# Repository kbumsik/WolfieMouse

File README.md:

# WolfieMouse

WolfieMouse is a robotics project to build [a micromouse](https://en.wikipedia.org/wiki/Micromouse). This project covers three parts:

* Robotics algorithm for maze solving (C++)
* low-level hardware driver software (C and ARM assembly)
* Tools to capture and plot robot's sensor data (Python)
* Embedded hardware design and PCB design (KiCad, an open-source alternative to Altium)

This robot won:
  * **The Special Mention Award in 2018 IEEE Region 1 Micromouse Robotics Competition**.
  * **The 3rd Place Award in 2019 IEEE Region 1 Micromouse Robotics Competition**.

## Get started

If you don't know what is micromouse competition, [this document will help.](doc/What-is-Micromouse.md).

Requires tools:
* [GNU Arm Embedded Toolchain](https://developer.arm.com/open-source/gnu-toolchain/gnu-rm) and [Makefile](https://www.gnu.org/software/make/manual/make.html) to build program for the robot.
* [OpenOCD](http://openocd.org/) to upload the program to the robot and to debug.
* [KiCad](http://kicad.org/) to design a PCB hardware.

Otherwise, a [Vagrant](https://www.vagrantup.com/) virtual machine environment is provided to skip installing the above tools.

If you whish to start with this project, see [get stared document](doc/Get-started.md).

## Documentation

See [documentation section.](doc/)

## Directory descriptions

* `doc`: Documentation folder
* `firmware`: The robot's program folder, including robotics algorithms and hardware drivers
* `simulation`: Programs to test algorithms on a desktop computer
* `tools`: Contains robot sensor data capturing tools and scripts for Vagrant machine.

## Gallery

Terminal-based simulation program. `M` stands for the position of the robot, `D` stands for the position of the goal in the maze, and `S` stands for the starting position.

Schematic overview.

PCB Footprint overview.

## License and Credits

Source code in `firmware` and `simulation` folders are licensed under [GPLv2.1](https://www.gnu.org/licenses/old-licenses/lgpl-2.1.en.html).

External libraries (FreeRTOS, CMSIS, STM32F4 HAL) under `firmware/lib` follow their own terms.

The fundamental hardware design is inspired by [Project Futura](http://micromouseusa.com/?page_id=1342) by [Green Ye](http://www.greenye.net/).

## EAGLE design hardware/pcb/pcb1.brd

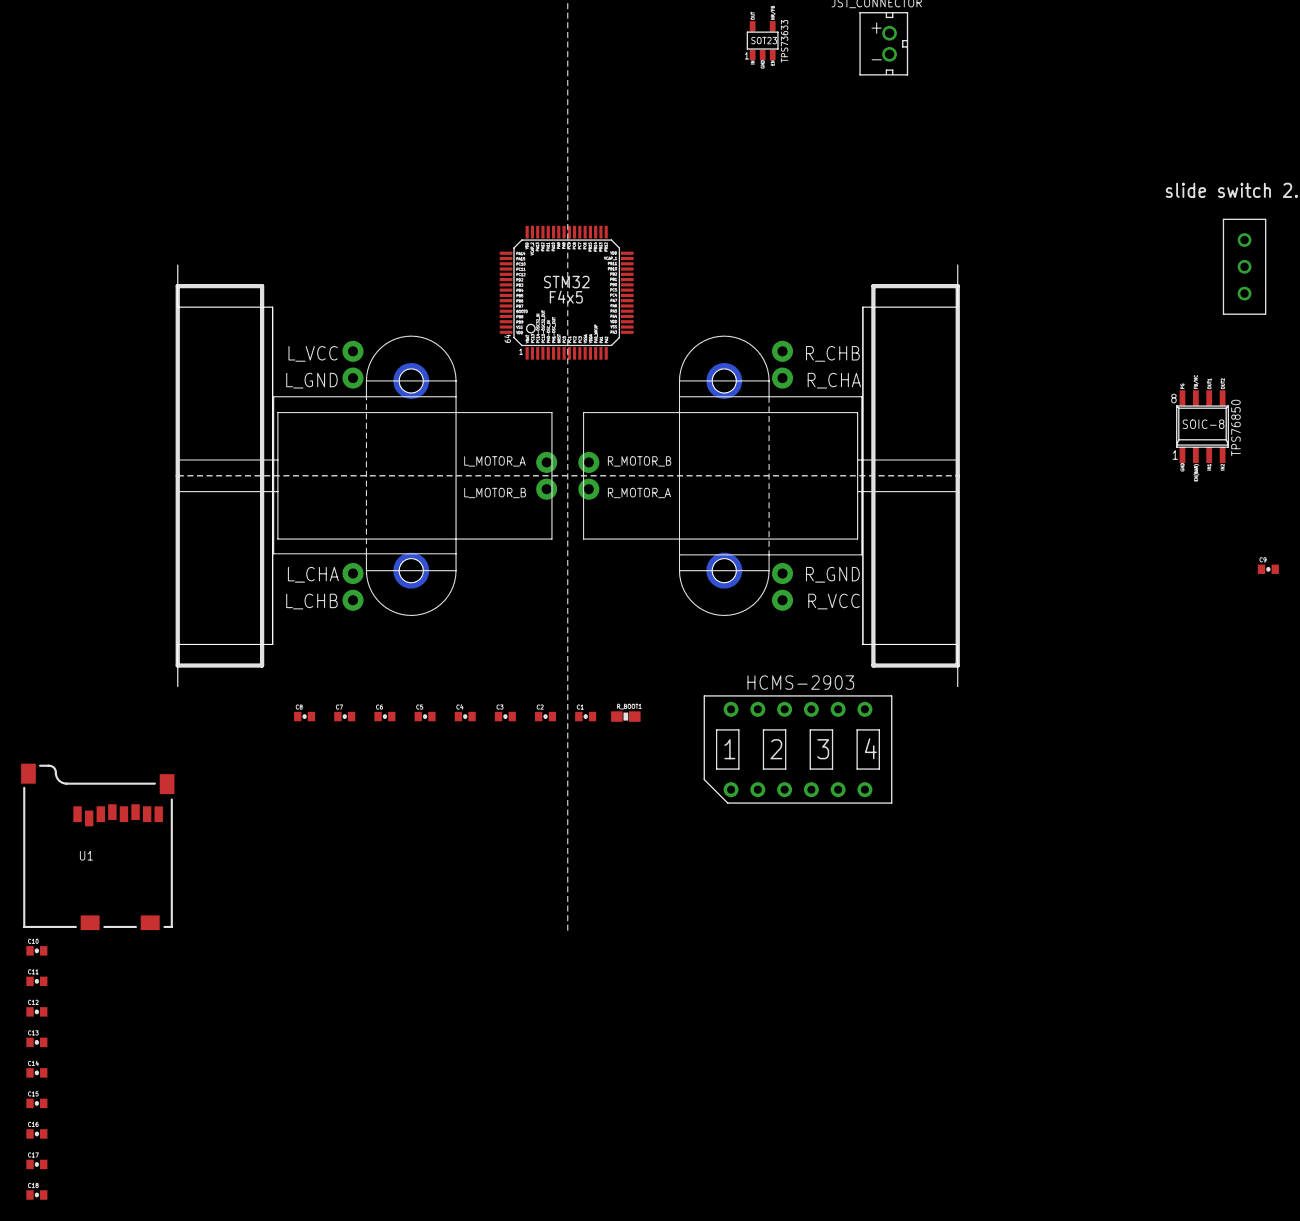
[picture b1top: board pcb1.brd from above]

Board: 2 copper layers, 27 parts (0 on the bottom side), 14 nets, no tracks yet.

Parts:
C1, C8: 2.2uF; 0402-CAP
C2, C3, C6, C7, C9, C10, C11, C12, C13, C14, C15, C16, C17, C18: 0.1uF; 0402-CAP
C4, C5: 4.7uF; 0402-CAP
R_BOOT1: 47K; 0603-RES
U1: USD-SOCKETSMD; MICRO-SD-SOCKET-PP
U$1: FUTURA_V1.0_MOTOR_MOUNT; FUTURA_V1.0_MOTOT_MOUNT
U$2: STM32F405/415_LQFP64
U$3: TPS76850(SOIC-8)
U$4: TPS73633(SOT-23)
U$5: JST_CONNECTOR_FEMALE
U$6: TS02_SWITCH
U$7: HCMS-2903

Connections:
3.3V: C2.1, C3.1, C4.1, C5.1, C6.1, C7.2, C9.1, C14.2, C15.2, C16.2, U$2.VBAT, U$2.VDDA, U$2.VDD_0, U$2.VDD_1, U$2.VDD_2, U$2.VDD_3, U$4.NR/FB, U$4.OUT
5V: C17.2, C18.2, U$7.SEL, U$7.V_LOGIC
AGND: C5.2, C6.2, U$2.VSSA
DIS_CE: U$2.PC11, U$7.CE
DIS_DATA_IN: U$2.PB5, U$7.DATA_IN
DIS_RESET: U$2.PC10, U$7.RESET
DIS_RS: U$2.PD2, U$7.RS
GND: C1.2, C2.2, C3.2, C4.2, C7.1, C8.1, C9.2, C10.1, C11.1, C14.1, C15.1, C16.1, C17.1, C18.1, U$2.VSS_0, U$2.VSS_1, U$3.EN(BAR), U$3.GND, U$4.GND, U$5.-, U$7.BLANK, U$7.GND
unnamed: U$5.+, U$6.PIN2
unnamed: C1.1, U$2.VCAP_2
unnamed: C8.2, U$2.VCAP_1
unnamed: R_BOOT1.1, U$2.PB10
unnamed: C12.2, C13.2, U$3.OUT1, U$3.OUT2, U$4.EN, U$4.IN
V_BAT: C10.2, C11.2, U$3.IN1, U$3.IN2, U$6.PIN3

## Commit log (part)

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2016-01-18 updated basic CubeMX project
2016-01-19 updated working test project
2016-02-02 Added simulation and algorithm part - 80% completed.
2016-02-08 updated MouseController.cpp
2016-02-09 reverted the changes back
    --eric
2016-02-29 added example_main.cpp
2016-03-31 updated PCB design
2016-03-31 PCB updated
2016-04-04 Finished the PCB
2016-04-04 Fixed for the PCB manufacturer requirements
2016-04-05 Uploaded bill of materials
2016-04-06 The range finder is all working. Integrating MUX needed
2016-04-06 Changed the PCB design to meet the manufacturer's requirement
2016-04-08 Compilation good
2016-04-08 Applied Formatter
2016-04-09 Printing and Saving simulation Good
2016-04-10 Floodfill algorithm good
2016-04-11 1. C++ object initialization problem fixed 2. Queue is working well. 3. But path algorithm needs work. it does not reach to the goal
2016-04-15 1. added the main project 2. changed the freq of the MCU, just for a while
2016-04-15 all four Range finders working well
2016-04-15 added LED pins
2016-04-15 saved-encoder and motor
2016-04-16 Motor driver OK
2016-04-16 1.Rotary encoder works well 2.The measurements is added
2016-04-16 updated test project
2017-01-05 2017 Micromouse initial setup start
2017-01-06 added vagrantfile
2017-01-08 Added Makefile
2017-01-10 wrote a Dockerfile (incomplete)
2017-01-14 provisioning for GNU ARM Eclipse
2017-01-14 Added RDP/VNC server. All Vagrant/VirtualBox configurations are set.
2017-01-15 Fixed Eclipse mars hanging problem with GTK3
2017-01-15 Changed macro name and position
2017-01-16 Applied Linux style coding convention. Separate Enum and Struct to their own file.
2017-01-16 Modified README.md
2017-01-16 Fixed some markdown typo
2017-01-16 Fixed enum convention for C++
2017-01-18 Only moved order of definitions to improve readability
2017-01-18 Deleted init() functions in each class, using C++11 style delegating constructor.
2017-01-21 Add Gitter badge
2017-01-24 added .gitattributes
2017-01-24 updateCell() replaced with printMaze() in MouseController class. printMaze() overrides printMaze method in the MazeIO class
2017-01-24 printMaze in Maze class was made virtual
2017-01-24 change the name of class design directory
2017-01-24 added class design documentation
2017-01-24 Resolved some compiler warnings (initialization list order and compound literal)
2017-02-05 Merged finder and interface implementation classes
2017-02-05 Added hardware designs
2017-02-06 changed structure of documentation
2017-02-07 Fixed broken image
2017-02-07 changed PNG file with JPG
2017-02-07 Add them again
2017-02-07 Try deleting again after fixing .gitattributes
2017-02-08 A draft of report.
2017-02-08 added What-is-micromouse
2017-02-14 chagned Vagrant script
2017-02-14 added more instructions
2017-02-15 fixed Makefile
2017-02-16 Deleted unnesecessary script folder
2017-02-16 Added kb-lib
2017-02-16 Fixed Vagrant file
2017-02-16 updated kb-lib for Makefile
2017-02-16 attendace file added
2017-02-16 I changed ATENDEE.ed
2017-02-17 Completed writing GIthub-HOWTO
2017-02-17 Added hardware design document
2017-02-22 Added design goal for v2.0 and 3D models
2017-03-05 FIxed the invalid cell problem. New function was added to the Maze.hpp.
2017-03-05 Added empty Finder and Mover Interfaces
2017-03-10 Changed Pop/push order and a decision on adjacent cell
2017-03-10 Maze.hpp: Added methods for Position struct
2017-03-10 Applied to MouseController.cpp
2017-03-11 Made it so that the mouse points in the direction it is going
2017-03-11 Coding conventions kept and code simplified
2017-03-16 added experimental PyTTY.
2017-03-17 4 goals are supported now in algorith and maze class.
2017-03-17 destinations member in MouseController class was configured. The algorithm uses destinations now and boolean methods were added. Maybe we can add another method to add destinations.
2017-03-18 Hardware driver cleanup
2017-03-19 Default goals only added when no file is loaded. Otherwise goals from file are used
2017-03-19 Destinations fully implemented. The mouse will set the goals as destinations at initialization. The algorithm will find destinations one by one and the mouse will move to each one until reaching the 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
2017-03-19 Enabled FreeRTOS and onButtonPressed event for blinky project
2017-03-21 Improved encoder update scheme
2017-03-21 Change name of peripherals.c
2017-03-22 Added a new pcb board folder
2017-03-29 added BlackWolf hardware project - on progress!
2017-03-30 BlackWolf PCB design completed
2017-03-30 PCB into production. Directory cleanup
2017-03-30 Mouse will go to goal then it will explore 4 unsearched cells then it will go home. It will repeat this.
2017-03-30 small fix
2017-04-02 Improved encoder update scheme
    Change name of peripherals.c
    Added simple pid control
2017-04-02 minor fix on initializing.
2017-04-04 FSM was implamented. The mouse is in three states. goGoal, explore, goStart.
2017-04-05 Divided project directory into boards
2017-04-05 added a simple sensor test in Nucleo-blinky
2017-04-06 Algorithm runs only when it new data of a cell is found
2017-04-07 Speed-based PID PWM control updated
2017-04-07 Added range sensr-based rotational PID control
2017-04-07 Provide system function for convenient control
2017-04-07 added skeleton main FSM
2017-04-07 Added going straight test to the FSM
2017-04-08 updated kb_lib
2017-04-08 This is the last code for the competition
2017-04-20 deleted unnessccary bsp
2017-04-20 Changed object model of motor and encoder
2017-04-22 Implemented turning operation for motion control
2018-03-07 PCB: Fixed wrong NMOS pinmap
2018-03-07 PCB: Fixed floating PWM output problem
2018-03-08 PCB: Separated 5V source due to heat
2018-03-08 PCB: Added Via Stitching
2018-03-15 CAM created
2018-03-15 Added VS code workspace
2018-03-15 Added latest STM32F4 HAL from kb_lib
2018-03-15 Added latest FreeRTOS from kb_lib
2018-03-15 Hardware: Updated STM32CubeMX project to remove fatfs
2018-03-15 Changed kb_lib path
2018-03-15 Changed kb_lib submodule to plain directory
2018-03-16 Deleted kb_lib, moving components to firmware folder
2018-03-16 Reordered projects folder, moving firmware sources
2018-03-16 FIrmware: FIrst Makefile blinky project (NOT PERFECT YET)
2018-03-16 Makefile: Now it covers all components
2018-03-16 System_stm32f4xx.c updated to the latest
2018-03-16 Blinkey: First successful flashing to WolfieMouse board using Makefile
2018-03-16 Deleted outdated main_project
2018-03-17 Env: Updated Vagrant environment. Cleanup some settings files
2018-03-17 Added the project's root Makefile
2018-03-18 modified comment for the test
2018-03-18 Revert 29ab2d , Created Makefile porject for Simuation.
2018-03-18 Simul: Reverted out.txt
2018-03-18 Changed cpp file to cc
2018-03-18 Simul: check if files exists
2018-03-19 Tool: fixed /usr/local/sbin:/usr/local/bin:/usr/bin:/usr/lib/emscripten:/usr/lib/jvm/default/bin:/usr/bin/site_perl:/usr/bin/vendor_perl:/usr/bin/core_perl:/home/kbumsik/opt/emsdk-portable:/home/kbum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
2018-03-19 Blinky: Added Measuring rotary encoder
2018-03-20 Encoder: changed to struct based
2018-03-20 Range: separated .c file for range sensor
2018-03-21 edit pathfinder using char
2018-03-21 using enum and modified algorithms
2018-03-22 Simul: Changed enum characters for readiability
2018-03-22 left, right turn case during moving horizontal algorithm fix
2018-03-22 PID: set parameters for mouse. Working well
2018-03-22 adjust algorithm about locationg mouse to the center
2018-03-22 remove vscode setting.json
2018-03-23 removed out.txt file
2018-03-23 Forgot to switch the functions in main
2018-03-23 Mouse: Added Thread based motor control, not interrupt
2018-03-23 Modified the linker as to reserve sector 1. sector 0 cannot be used. Test program created and verified proper reading
2018-03-23 IMPORTANT: Best PID for forward moving, PWM frequency, baud rate changes
2018-03-23 direction coordinate modified(memory -> Decart)
2018-03-23 re upload after coordinate swap
2018-03-24 Cmd: Added smooth turn (not perfect) and "back start to center" commands
2018-03-24 segmentaition fault(core dumped) fix
2018-03-24 PID: added header file
2018-03-24 FlashIO class added. this will make it possible for our mouse to save and read data from flash
2018-03-24 Tools: Added Jlink OB, and stdc++ lib
2018-03-24 Created competition mouse, fixed RealMouse
2018-03-24 Polling control of mouse
2018-03-24 Quick fix
2018-03-27 Fixed SimulMouse
2018-03-28 Firmware: source cleanup
2018-03-28 .vscode: Deleted Windows and Mac settings
2018-03-28 Doc: updated Readme.md
2018-03-31 Makefile: Added Windows Subsystem for Linux (WSL) support
2018-04-01 simulation: Deleted out.txt
2018-04-01 Makefile: cleanup
2018-04-02 VS Code: Added full support for debugging in VS Code
2018-04-08 IOInterface: Added IOInterface::read()
2018-04-08 Simul: added string-contructed maze example
2018-04-08 Blinky_wolfimouse: Now it can run simulation
2018-04-08 MazeIO: now it correctly detects if maze data exists
2018-04-08 flash: Fixed first earsing failed problem
2018-04-08 FlashIO: Added to blinky_nucleo
2018-04-09 MouseController: Fixed bug on moving, Introduced scanAndMove() to reduce redundant codes
2018-04-09 MouseController: reorder methods
2018-04-09 Maze: fixed some compiler warnings
2018-04-09 MouseController: Fixed the mouse hangs when all destination reached
2018-04-09 Fixed some compiler warnings
2018-04-10 Firmware: Deleted system_control.h
2018-04-10 CMD: Added range sensor reading (UNTESTED)
2018-04-11 PathFinder: now it prints the three cases
2018-04-11 Pathfinder: duplication counting
2018-04-12 Added clang-format
2018-12-21 Create To do
2019-03-01 Updated for 2019
2019-03-01 Add leading project_ for project folders
2019-03-01 Add YouTube videos for installing software.
2019-03-02 Rename: blinky_nucleo64 => simulation_nucleo64
2019-03-02 Re-organize FSM table
2019-03-03 Main: Change FreeRTOS task name => thread to avoid name confilct with FSM tasks
2019-03-03 Main: change the naming conventions
2019-03-03 VSCode-CppTools: Deleted hard-coded includePath
2019-03-03 Main: merge with maze_solver
2019-03-03 Main: Separated button handling functions
2019-03-04 Main: Show task numbers on LED
2019-03-04 Terminal: Add more baud rate options
2019-03-04 VSCode: Updated include path for windows
2019-03-05 Control_loop: Use inline functions instead of FreeRTOS macros for readability
2019-03-05 Main: Implement basic tasks
2019-03-05 Main: Add descriptions of each tasks
2019-03-05 Control_loop: change the order of cmd_type enum
2019-03-06 Logger: First logger implementation
2019-03-06 src: moved some headers in board to module (without modification)
2019-03-06 project_blinky_wolfiemouse: Deleted
2019-03-06 Revert "Project reorganization: Moved project-specific codes to the common src folder"
2019-03-06 Fix logger
2019-03-06 Logger: Add logger test to simulation_nucleo64
2019-03-06 Log: updated plot.py to visualize
2019-03-07 Fix incorrect priority settings #73
2019-03-07 FSM: Fix issue with running next state's task instead of the current state.
2019-03-08 Turn off logger for performance reason
2019-03-08 Tools: Plot data over time
2019-03-08 FreeRTOS: use configUSE_PORT_OPTIMISED_TASK_SELECTION
2019-03-08 Rename: control_loop_thread_wait_until_1ms() => control_loop_thread_wait_1ms()
2019-03-08 Add CMD_MOVE_UNTIL_FRONT_WALL
2019-03-09 Plot.py: Last update
2019-03-09 update PID
2019-03-09 config_measurements.h: Move header to control_loop_thread_dirver.c
2019-03-09 Control_loop call xQueueSend inside of control_loop instead of cmd.d
2019-03-09 Add CMD_SENSOR_GET_RANGE and delete global range data
2019-03-09 cmd: change name CMD_LOW_* => CMD_NONBLOCK_*
2019-03-09 Control_loop: reduced size of queue
2019-03-09 MouseController: Add Optimizer, but not using it yet
2019-03-09 Added Move_until_wall
2019-03-09 Turn off side ranges when closing to the front wall
2019-03-09 Range: change name: front -> front_left
2019-03-10 Control_loop_thread: move peripheral initilization code to system_config.c
2019-03-10 Control_loop_thread.c: Moved to src/module
2019-07-04 Add fish shell for Vagrant, add Alacritty config
2019-07-07 Vagrant: Add USB serial kernel modules
2019-08-06 Vagrant: switch to zsh environment, add CoolTerm
2019-08-08 Vagrant: Add common config.sh, move bashrc=>zshrc
2019-08-08 Simulation: Add control loop

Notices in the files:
parts and their libraries:
SparkFun: Licensing: CC v3.0 Share-Alike You are welcome to use this library for commercial purposes.
